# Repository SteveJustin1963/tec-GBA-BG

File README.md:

# tec-TEC1-Custom-BG
Tec-1 PCB with GBA cartridge system + CPLD  by Ben Grimmett
- see also https://github.com/SteveJustin1963/tec-CPLD-BG

### features
- TEC ROM/RAM card 
- 4mbytes banked Flash
- 32 kbytes Banked NVRAM
- Just a suggestion for a proven, cheap, robust, plentiful supply of hot swappable memory cards for a future TEC-1.

### Memory map:
```
0x0000-3FFF fixed to Flash Address 0x0000-3FFF
0x4000-7FFF 256 banks, can be swapped by writing to address 0x2000.
0xA000-BFFF 8kbytes of NVRAM.
```
- Write protected unless `0x0A` written to `0x0000`. Protected if any other value is written to that address. 
- Bank swapped by writing to `0x4000`

This still gives you empty spots in the memory map for other things, and the entire cart can be disabled with a /CS signal, or just unplugged. These are common bootleg GameBoy Cartridges. Z80-like code executes directly from them in the GB. You can find them on eBay or aliexpress from $4 shipped to your door.

### How do you get code on them? 
You can do it in system, or use any number of GB Cart flashers like the pic included. The cart appears as a USB mass storage drive, you drag the firmware on, and its done. Not sure you can beat the bang for buck these offer. Cart sockets are $1 ea and with HUGE pins, soldering won't be a problem.

### buy from Benn (Goulburn NSW):
- 4Mbyte Flash + 32K save (volatile) - https://bennvenn.myshopify.com/.../gb-c-flash-cart-4mbyte...
- 4Mbyte + 32K battery backed (NV) - https://bennvenn.myshopify.com/.../gb-c-flash-cart-4mbyte...
- The best cart flasher you can buy! (USB Drag and drop, no drivers, no software) - https://bennvenn.myshopify.com/.../usb-gb-c-cart-dumper...
- Cart Sockets: https://bennvenn.myshopify.com/.../32pin-gb-c-a-cart...
- https://bennvenn.myshopify.com/products/usb-gb-c-cart-dumper-the-joey-jr

### slowboat from china:
- 4M + 32K NV - https://www.aliexpress.com/item/4000589108517.html...
AVOID CHINESE FLASHERS - they're all clones of ours or others and have adopted the nickname 'firestarters' for a good reason. A cheaper flasher is the GBxRW from Inside Gadgets. Another Aussie company. A little slower, a little more clunky but you'll save $10 or so, they don't support some chinese carts.
Chinese cart socket - https://www.aliexpress.com/item/4001322498055.html...

### BG; Finished!
```
0x0000-07FF EPROM
0x0800-0FFF SRAM
0x1000-17FF expansion dip
0x4000-7FFF 4mbytes of flash
0xA000-BFFF 32kbytes nvram
```
### features
- Reproduced the keypad IC in VHDL with debounce filtering.
- Errors: silkscreen Rom and ram locations are swapped. 
- Fixed in CPLD but a wr wire added. If I didn't solder the sram in I could have swapped sockets.
- Keypad matrix pull-ups needed, the max3000 family of CPLD don't support internal pull-ups. 
- Fitted in the column pads instead. Could use a network resistor for a neater finish.
- And jtag #2 and jtag #3 ports are swapped.
- Need to add resistors to satisfy MonB code or fix the routine.
- Can execute code from gameboy cart!
- 4 PCBs up for grabs. $25plus post and I'll solder in the CPLDs and 3.3v reg and flash the code to them.  

### info

The TEC-1 is a tec-compatible computer with a GB (Game Boy) cart slot to make use of a GB carts huge ROM and nvRAM capacity. It won't play GB games. The idea behind this is to help you learn how to code CPLD's. BG; I don't have that many spare Z80's or other bits and pieces for full kits. They will include the CPLD's though, pre soldered and programmed. A cpld is a fpga, just a different name (and other differences). Programming needs a $10 usb programmer from ebay (USB Blaster). As for the code, you can use the visual designer where you just drag logic chips and draw wires, or you can code in a specific language. I'll upload all the code here.

Using a CPLD for address decoding for example means you can fully reconfigure the memory map in seconds and it doesn't have the same issues the original TEC did with address decoding. You can also change how the 7seg driver works, the TEC must constantly refresh the LED's, you *could* code a driver in the CPLD to do that for you to free up the z80 for more important things. And finally, the keypad CPLD - it emulates the original chip but it can also be expanded to hundreds of keys, or even a ps2 keyboard.

Can a FPGA be made to emulate a 74C923? If so, can you get FPGAs in 20 pin DIP (or SOIC) packages ? Yes, the second CPLD on the board emulates the '923 and heaps of room to spare. I've got some dip PCBs coming in a week that'll convert the qfp package to dip 28. The circuit will be upload.

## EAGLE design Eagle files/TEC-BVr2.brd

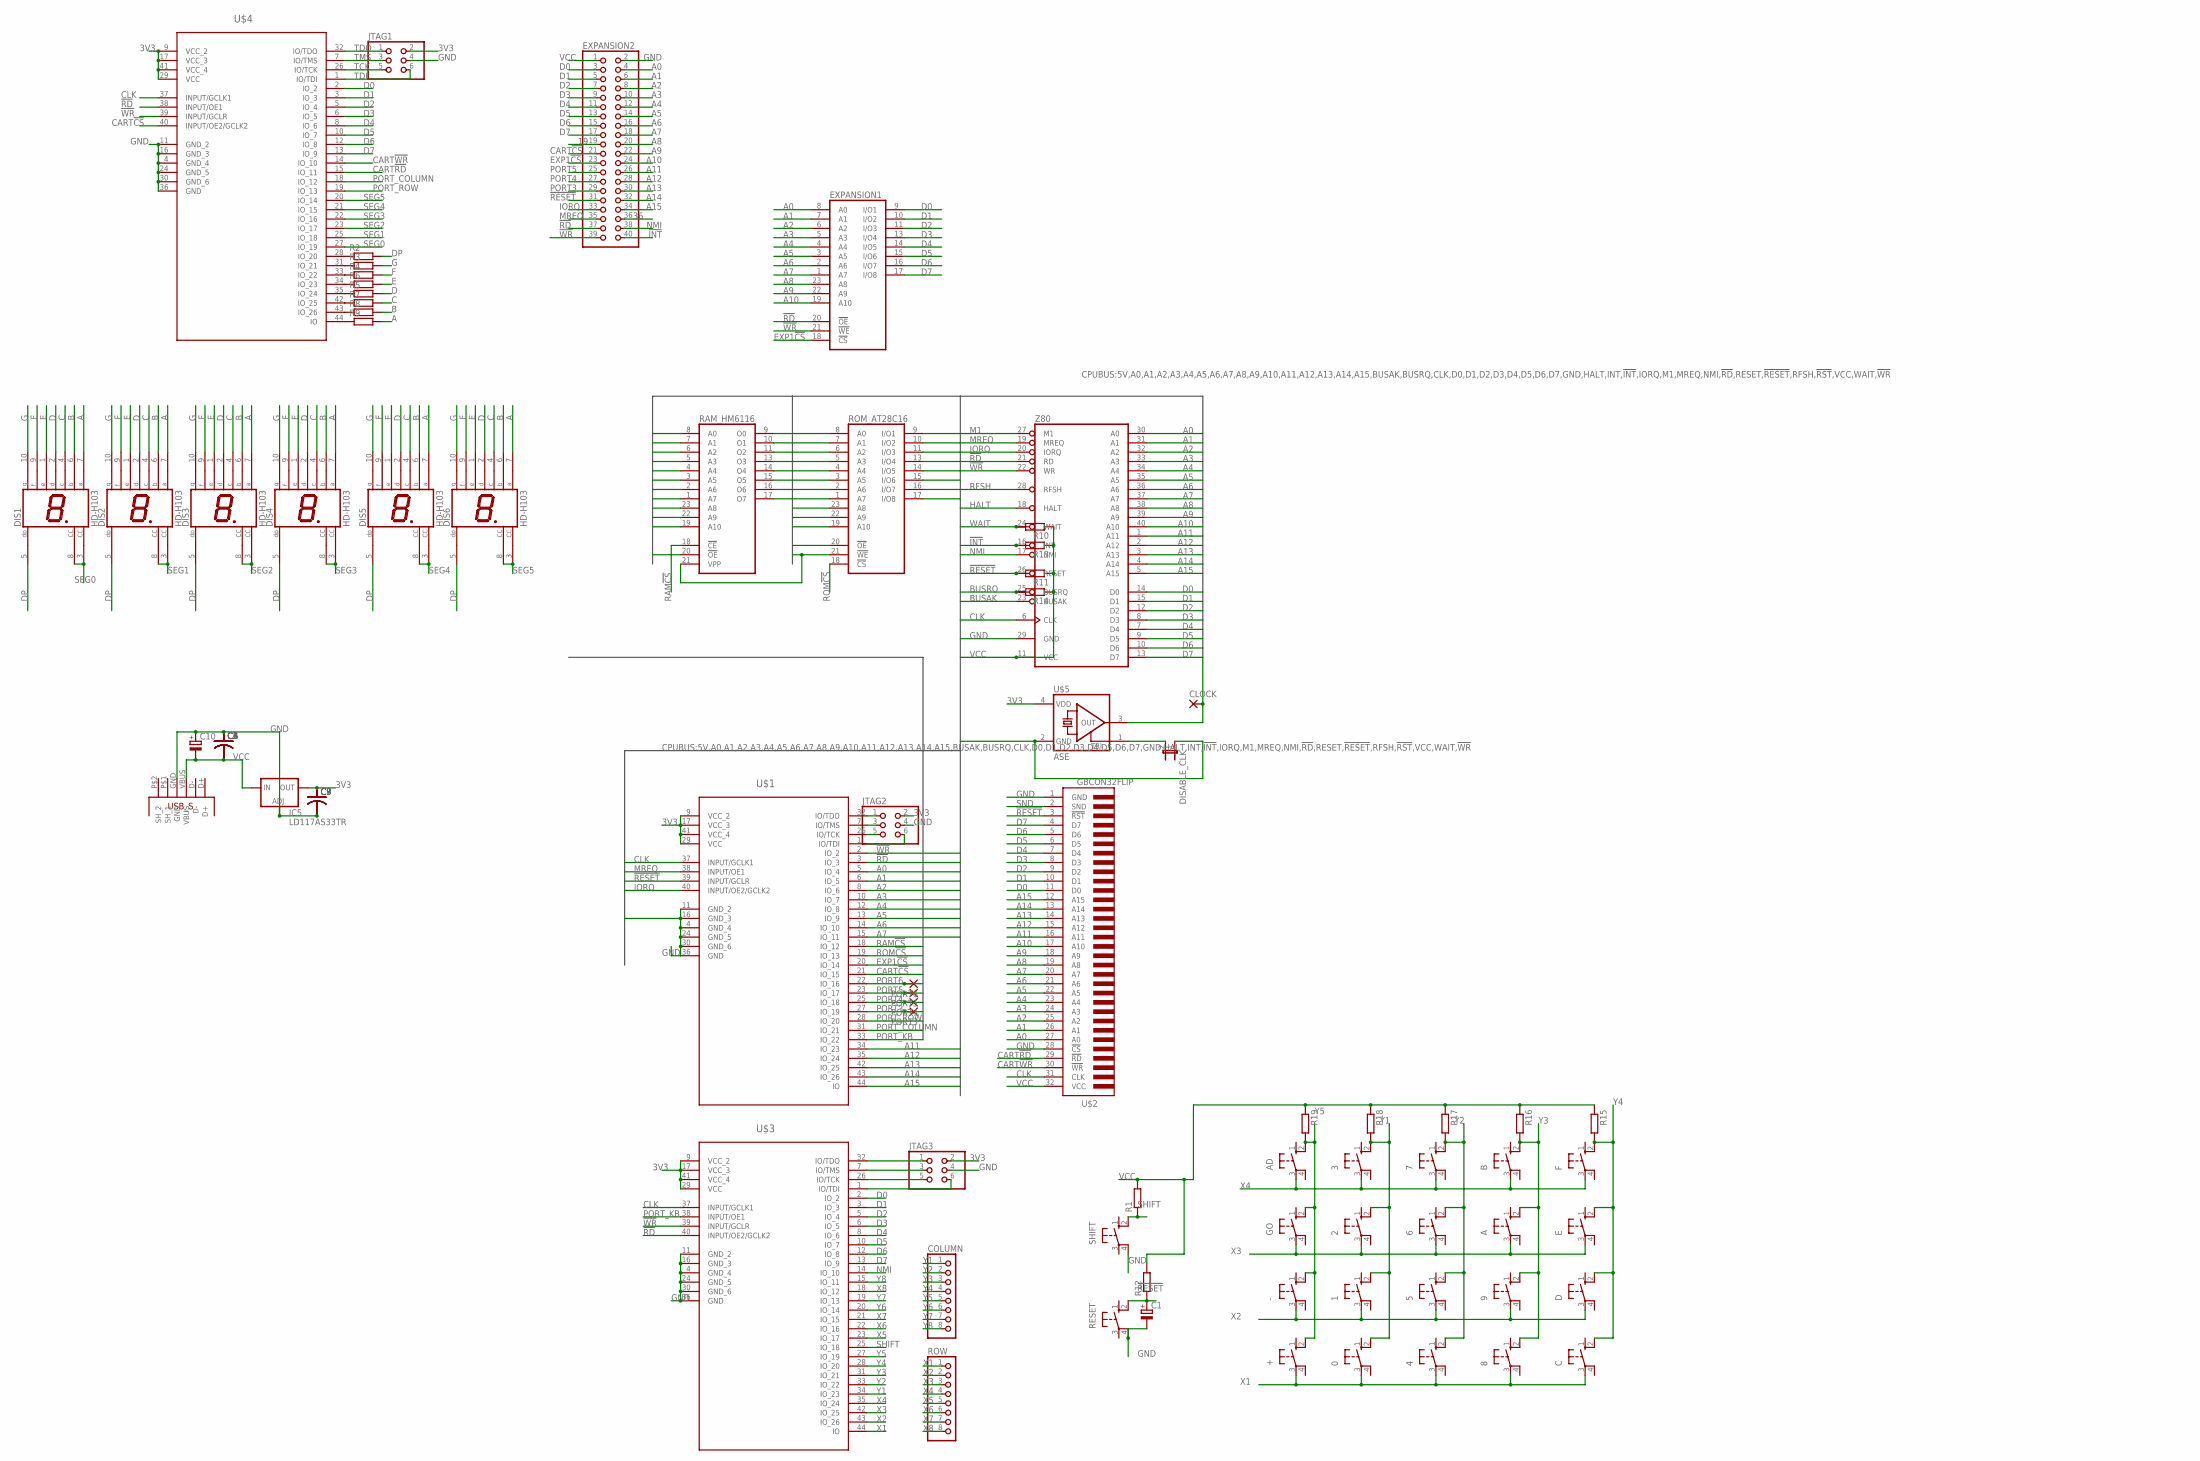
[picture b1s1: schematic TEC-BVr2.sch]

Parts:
0, 1, 2, 3, 4, 5, 6, 7, 8, 9: 10-XX; B3F-10XX
+: 10-XX; B3F-10XX
-: 10-XX; B3F-10XX
A: 10-XX; B3F-10XX
AD: 10-XX; B3F-10XX
B: 10-XX; B3F-10XX
C: 10-XX; B3F-10XX
C1, C10: CPOL-EUE2,5-6E; E2,5-6E
C2, C3, C4, C5, C6, C7, C8, C9: C-US050-024X044; C050-024X044
CLOCK: 1,6/0,8
COLUMN: PINHD-1X8; 1X08
D: 10-XX; B3F-10XX
DIS1, DIS2, DIS3, DIS4, DIS5, DIS6: HD-H103; HDSP-M
DISABLE_CLK: JP1E; JP1
E: 10-XX; B3F-10XX
EXPANSION1: 6116P; DIL24-6
EXPANSION2: PINHD-2X20; 2X20
F: 10-XX; B3F-10XX
GO: 10-XX; B3F-10XX
IC5: LD117AS33TR; SOT223
JTAG1, JTAG2, JTAG3: PINHD-2X3; 2X03
PORT3, PORT4, PORT5, PORT6: 1,6/0,8
R1, R2, R3, R4, R5, R6, R7, R8, R9, R10, R11, R12, R13, R14: R-EU_0207/12; 0207/12
R15, R16, R17, R18, R19: R-EU_0204/7; 0204/7
RAM_HM6116: 2716; DIL24
RESET: 10-XX; B3F-10XX
ROM_AT28C16: 6116P; DIL24-6
ROW: PINHD-1X8; 1X08
SHIFT: 10-XX; B3F-10XX
U$1: Address Decoding; QFP80P1200X1200X120-44N
U$2: GBCON32FLIP; GB_CON32
U$3: Keyboard Decoding; QFP80P1200X1200X120-44N
U$4: Display Decoding; QFP80P1200X1200X120-44N
U$5: ASE
U$6: USB; USB_B_PTH
Z80: Z80CPU; DIL40

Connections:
3V3: C7.1, C8.1, C9.1, IC5.4 (OUT), JTAG1.2, JTAG2.2, JTAG3.2, U$1.9 (VCC_2), U$1.17 (VCC_3), U$1.29 (VCC), U$1.41 (VCC_4), U$3.9 (VCC_2), U$3.17 (VCC_3), U$3.29 (VCC), U$3.41 (VCC_4), U$4.9 (VCC_2), U$4.17 (VCC_3), U$4.29 (VCC), U$4.41 (VCC_4), U$5.4 (VDD)
19: EXPANSION2.19
36: EXPANSION2.36
!INT: EXPANSION2.40, R13.2, Z80.16 (INT)
!RD: EXPANSION1.20 (!OE), EXPANSION2.37, RAM_HM6116.20 (!OE), ROM_AT28C16.20 (!OE), U$1.3 (IO_3), U$3.40 (INPUT/OE2/GCLK2), U$4.38 (INPUT/OE1), Z80.21 (RD)
!RESET: C1.+, EXPANSION2.31, R11.2, R12.1, RESET.2 (S1), U$1.39 (INPUT/GCLR), U$2.3 (!RST), Z80.26 (RESET)
!WR: EXPANSION1.21 (!WE), EXPANSION2.39, RAM_HM6116.21 (VPP), ROM_AT28C16.21 (!WE), U$1.2 (IO_2), U$3.39 (INPUT/GCLR), U$4.39 (INPUT/GCLR), Z80.22 (WR)
A: DIS1.7 (A), DIS2.7 (A), DIS3.7 (A), DIS4.7 (A), DIS5.7 (A), DIS6.7 (A), R9.2
A0: EXPANSION1.8 (A0), EXPANSION2.4, RAM_HM6116.8 (A0), ROM_AT28C16.8 (A0), U$1.5 (IO_4), U$2.27 (A0), Z80.30 (A0)
A1: EXPANSION1.7 (A1), EXPANSION2.6, RAM_HM6116.7 (A1), ROM_AT28C16.7 (A1), U$1.6 (IO_5), U$2.26 (A1), Z80.31 (A1)
A2: EXPANSION1.6 (A2), EXPANSION2.8, RAM_HM6116.6 (A2), ROM_AT28C16.6 (A2), U$1.8 (IO_6), U$2.25 (A2), Z80.32 (A2)
A3: EXPANSION1.5 (A3), EXPANSION2.10, RAM_HM6116.5 (A3), ROM_AT28C16.5 (A3), U$1.10 (IO_7), U$2.24 (A3), Z80.33 (A3)
A4: EXPANSION1.4 (A4), EXPANSION2.12, RAM_HM6116.4 (A4), ROM_AT28C16.4 (A4), U$1.12 (IO_8), U$2.23 (A4), Z80.34 (A4)
A5: EXPANSION1.3 (A5), EXPANSION2.14, RAM_HM6116.3 (A5), ROM_AT28C16.3 (A5), U$1.13 (IO_9), U$2.22 (A5), Z80.35 (A5)
A6: EXPANSION1.2 (A6), EXPANSION2.16, RAM_HM6116.2 (A6), ROM_AT28C16.2 (A6), U$1.14 (IO_10), U$2.21 (A6), Z80.36 (A6)
A7: EXPANSION1.1 (A7), EXPANSION2.18, RAM_HM6116.1 (A7), ROM_AT28C16.1 (A7), U$1.15 (IO_11), U$2.20 (A7), Z80.37 (A7)
A8: EXPANSION1.23 (A8), EXPANSION2.20, RAM_HM6116.23 (A8), ROM_AT28C16.23 (A8), U$2.19 (A8), Z80.38 (A8)
A9: EXPANSION1.22 (A9), EXPANSION2.22, RAM_HM6116.22 (A9), ROM_AT28C16.22 (A9), U$2.18 (A9), Z80.39 (A9)
A10: EXPANSION1.19 (A10), EXPANSION2.24, RAM_HM6116.19 (A10), ROM_AT28C16.19 (A10), U$2.17 (A10), Z80.40 (A10)
A11: EXPANSION2.26, U$1.34 (IO_23), U$2.16 (A11), Z80.1 (A11)
A12: EXPANSION2.28, U$1.35 (IO_24), U$2.15 (A12), Z80.2 (A12)
A13: EXPANSION2.30, U$1.42 (IO_25), U$2.14 (A13), Z80.3 (A13)
A14: EXPANSION2.32, U$1.43 (IO_26), U$2.13 (A14), Z80.4 (A14)
A15: EXPANSION2.34, U$1.44 (IO), U$2.12 (A15), Z80.5 (A15)
B: DIS1.6 (B), DIS2.6 (B), DIS3.6 (B), DIS4.6 (B), DIS5.6 (B), DIS6.6 (B), R8.2
BUSAK: Z80.23 (BUSAK)
BUSRQ: R14.2, Z80.25 (BUSRQ)
C: DIS1.4 (C), DIS2.4 (C), DIS3.4 (C), DIS4.4 (C), DIS5.4 (C), DIS6.4 (C), R7.2
CART!CS: EXPANSION2.21, U$1.21 (IO_15), U$4.40 (INPUT/OE2/GCLK2)
CART!RD: U$2.29 (!RD), U$4.15 (IO_11)
CART!WR: U$2.30 (!WR), U$4.14 (IO_10)
CLK: CLOCK.1, U$1.37 (INPUT/GCLK1), U$2.31 (CLK), U$3.37 (INPUT/GCLK1), U$4.37 (INPUT/GCLK1), U$5.3 (OUT), Z80.6 (CLK)
D: DIS1.2 (D), DIS2.2 (D), DIS3.2 (D), DIS4.2 (D), DIS5.2 (D), DIS6.2 (D), R5.2
D0: EXPANSION1.9 (I/O1), EXPANSION2.3, RAM_HM6116.9 (O0), ROM_AT28C16.9 (I/O1), U$2.11 (D0), U$3.2 (IO_2), U$4.2 (IO_2), Z80.14 (D0)
D1: EXPANSION1.10 (I/O2), EXPANSION2.5, RAM_HM6116.10 (O1), ROM_AT28C16.10 (I/O2), U$2.10 (D1), U$3.3 (IO_3), U$4.3 (IO_3), Z80.15 (D1)
D2: EXPANSION1.11 (I/O3), EXPANSION2.7, RAM_HM6116.11 (O2), ROM_AT28C16.11 (I/O3), U$2.9 (D2), U$3.5 (IO_4), U$4.5 (IO_4), Z80.12 (D2)
D3: EXPANSION1.13 (I/O4), EXPANSION2.9, RAM_HM6116.13 (O3), ROM_AT28C16.13 (I/O4), U$2.8 (D3), U$3.6 (IO_5), U$4.6 (IO_5), Z80.8 (D3)
D4: EXPANSION1.14 (I/O5), EXPANSION2.11, RAM_HM6116.14 (O4), ROM_AT28C16.14 (I/O5), U$2.7 (D4), U$3.8 (IO_6), U$4.8 (IO_6), Z80.7 (D4)
D5: EXPANSION1.15 (I/O6), EXPANSION2.13, RAM_HM6116.15 (O5), ROM_AT28C16.15 (I/O6), U$2.6 (D5), U$3.10 (IO_7), U$4.10 (IO_7), Z80.9 (D5)
D6: EXPANSION1.16 (I/O7), EXPANSION2.15, RAM_HM6116.16 (O6), ROM_AT28C16.16 (I/O7), U$2.5 (D6), U$3.12 (IO_8), U$4.12 (IO_8), Z80.10 (D6)
D7: EXPANSION1.17 (I/O8), EXPANSION2.17, RAM_HM6116.17 (O7), ROM_AT28C16.17 (I/O8), U$2.4 (D7), U$3.13 (IO_9), U$4.13 (IO_9), Z80.13 (D7)
DP: DIS1.5 (DP), DIS2.5 (DP), DIS3.5 (DP), DIS4.5 (DP), DIS5.5 (DP), DIS6.5 (DP), R2.2
E: DIS1.1 (E), DIS2.1 (E), DIS3.1 (E), DIS4.1 (E), DIS5.1 (E), DIS6.1 (E), R6.2
EXP1!CS: EXPANSION1.18 (!CS), EXPANSION2.23, U$1.20 (IO_14)
F: DIS1.9 (F), DIS2.9 (F), DIS3.9 (F), DIS4.9 (F), DIS5.9 (F), DIS6.9 (F), R4.2
G: DIS1.10 (G), DIS2.10 (G), DIS3.10 (G), DIS4.10 (G), DIS5.10 (G), DIS6.10 (G), R3.2
GND: C1.-, C2.1, C3.1, C4.1, C5.1, C6.1, C7.2, C8.2, C9.2, C10.+, DISABLE_CLK.1, EXPANSION1.12 (GND), EXPANSION2.2, IC5.1 (ADJ), JTAG1.4, JTAG2.4, JTAG3.4, RAM_HM6116.12 (GND), RESET.4 (P1), ROM_AT28C16.12 (GND), SHIFT.4 (P1), U$1.4 (GND_4), U$1.11 (GND_2), U$1.16 (GND_3), U$1.24 (GND_5), U$1.30 (GND_6), U$1.36 (GND), U$2.1 (GND), U$2.28 (!CS), U$3.4 (GND_4), U$3.11 (GND_2), U$3.16 (GND_3), U$3.24 (GND_5), U$3.30 (GND_6), U$3.36 (GND), U$4.4 (GND_4), U$4.11 (GND_2), U$4.16 (GND_3), U$4.24 (GND_5), U$4.30 (GND_6), U$4.36 (GND), U$5.2 (GND), U$6.GND, Z80.29 (GND)
HALT: Z80.18 (HALT)
IORQ: EXPANSION2.33, U$1.40 (INPUT/OE2/GCLK2), Z80.20 (IORQ)
M1: Z80.27 (M1)
MREQ: EXPANSION2.35, U$1.38 (INPUT/OE1), Z80.19 (MREQ)
unnamed: R2.1, U$4.28 (IO_20)
unnamed: R3.1, U$4.31 (IO_21)
unnamed: R4.1, U$4.33 (IO_22)
unnamed: R5.1, U$4.35 (IO_24)
unnamed: JTAG3.1, U$3.32 (IO/TDO)
unnamed: DISABLE_CLK.2, U$5.1 (TRI)
unnamed: JTAG3.3, U$3.7 (IO/TMS)
unnamed: R6.1, U$4.34 (IO_23)
unnamed: R7.1, U$4.42 (IO_25)
unnamed: R8.1, U$4.43 (IO_26)
unnamed: R9.1, U$4.44 (IO)
unnamed: JTAG3.5, U$3.26 (IO/TCK)
unnamed: JTAG3.6, U$3.1 (IO/TDI)
unnamed: JTAG2.1, U$1.32 (IO/TDO)
unnamed: JTAG2.3, U$1.7 (IO/TMS)
unnamed: JTAG2.5, U$1.26 (IO/TCK)
unnamed: JTAG2.6, U$1.1 (IO/TDI)
NMI: EXPANSION2.38, U$3.14 (IO_10), Z80.17 (NMI)
PORT3: EXPANSION2.29, PORT3.1, U$1.27 (IO_19)
PORT4: EXPANSION2.27, PORT4.1, U$1.25 (IO_18)
PORT5: EXPANSION2.25, PORT5.1, U$1.23 (IO_17)
PORT6: PORT6.1, U$1.22 (IO_16)
PORT_COLUMN: U$1.31 (IO_21), U$4.18 (IO_12)
PORT_KB: U$1.33 (IO_22), U$3.38 (INPUT/OE1)
PORT_ROW: U$1.28 (IO_20), U$4.19 (IO_13)
RAM!CS: RAM_HM6116.18 (!CE), U$1.18 (IO_12)
RFSH: Z80.28 (RFSH)
ROM!CS: ROM_AT28C16.18 (!CS), U$1.19 (IO_13)
SEG0: DIS1.3 (CC), DIS1.8 (CC), U$4.27 (IO_19)
SEG1: DIS2.3 (CC), DIS2.8 (CC), U$4.25 (IO_18)
SEG2: DIS3.3 (CC), DIS3.8 (CC), U$4.23 (IO_17)
SEG3: DIS4.3 (CC), DIS4.8 (CC), U$4.22 (IO_16)
SEG4: DIS5.3 (CC), DIS5.8 (CC), U$4.21 (IO_15)
SEG5: DIS6.3 (CC), DIS6.8 (CC), U$4.20 (IO_14)
SHIFT: R1.1, SHIFT.2 (S1), U$3.25 (IO_18)
SND: U$2.2 (SND)
TCK: JTAG1.5, U$4.26 (IO/TCK)
TDI: JTAG1.6, U$4.1 (IO/TDI)
TDO: JTAG1.1, U$4.32 (IO/TDO)
TMS: JTAG1.3, U$4.7 (IO/TMS)
VCC: C2.2, C3.2, C4.2, C5.2, C6.2, C10.-, EXPANSION1.24 (VCC), EXPANSION2.1, IC5.3 (IN), R1.2, R10.1, R11.1, R12.2, R13.1, R14.1, R15.1, R16.1, R17.1, R18.1, R19.1, RAM_HM6116.24 (VCC), ROM_AT28C16.24 (VCC), U$2.32 (VCC), U$6.VBUS, Z80.11 (VCC)
WAIT: R10.2, Z80.24 (WAIT)
X1: 0.3, 4.3, 8.3, +.3, C.3, ROW.1, U$3.44 (IO)
X2: 1.3, 5.3, 9.3, -.3, D.3, ROW.2, U$3.43 (IO_26)
X3: 2.3, 6.3, A.3, E.3, GO.3, ROW.3, U$3.42 (IO_25)
X4: 3.3, 7.3, AD.3, B.3, F.3, ROW.4, U$3.35 (IO_24)
X5: ROW.5, U$3.23 (IO_17)
X6: ROW.6, U$3.22 (IO_16)
X7: ROW.7, U$3.21 (IO_15)
X8: ROW.8, U$3.18 (IO_12)
Y1: 0.2 (S1), 1.2 (S1), 2.2 (S1), 3.2 (S1), COLUMN.1, R18.2, U$3.34 (IO_23)
Y2: 4.2 (S1), 5.2 (S1), 6.2 (S1), 7.2 (S1), COLUMN.2, R17.2, U$3.33 (IO_22)
Y3: 8.2 (S1), 9.2 (S1), A.2 (S1), B.2 (S1), COLUMN.3, R16.2, U$3.31 (IO_21)
Y4: C.2 (S1), COLUMN.4, D.2 (S1), E.2 (S1), F.2 (S1), R15.2, U$3.28 (IO_20)
Y5: +.2 (S1), -.2 (S1), AD.2 (S1), COLUMN.5, GO.2 (S1), R19.2, U$3.27 (IO_19)
Y6: COLUMN.6, U$3.20 (IO_14)
Y7: COLUMN.7, U$3.19 (IO_13)
Y8: COLUMN.8, U$3.15 (IO_11)

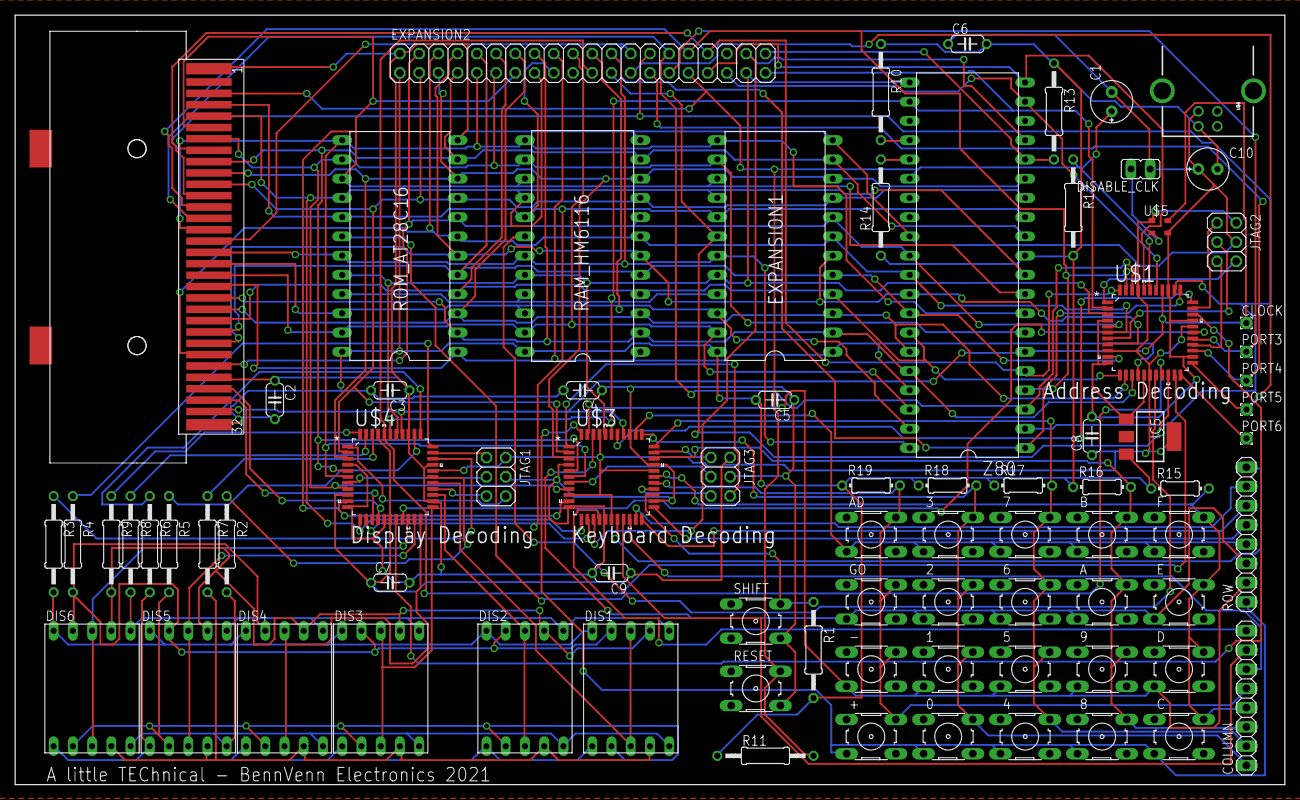
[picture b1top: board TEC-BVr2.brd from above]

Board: 2 copper layers, 167.6 x 101.6 mm, 80 parts (0 on the bottom side), 102 nets.
